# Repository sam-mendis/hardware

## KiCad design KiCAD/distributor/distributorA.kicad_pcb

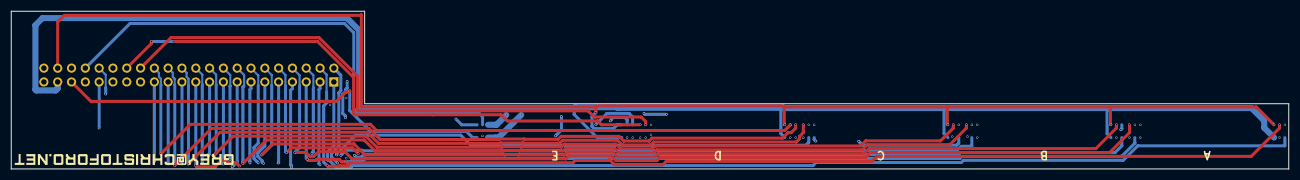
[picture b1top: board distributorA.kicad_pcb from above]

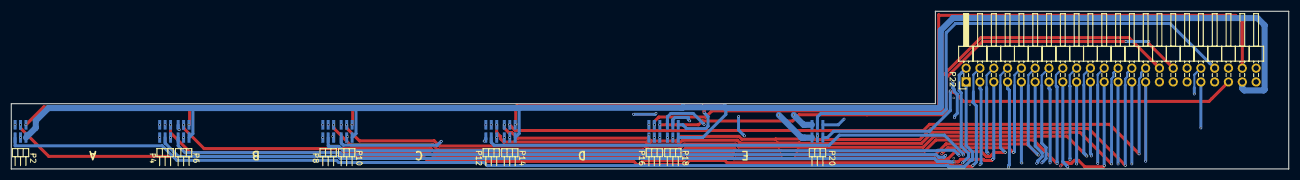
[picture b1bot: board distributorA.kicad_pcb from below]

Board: 4 copper layers, 235.0 x 29.0 mm, 11 parts (11 on the bottom side), 44 nets.

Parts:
P2, P4, P6, P8, P10, P12, P14, P16, P18, P20: CONN_02X03; FTMH-103-03-L-DH
P22: CONN_02X22; Pin_Header_Angled_2x22_Pitch2.54mm

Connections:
+3V3: P2.1, P6.1, P10.1, P14.1, P18.1, P22.41
+5V: P4.5, P8.5, P12.5, P16.5, P20.5, P22.43
A1_I: P2.3, P22.3
A1_V: P2.4, P22.4
A3_I: P4.3, P22.5
A3_V: P4.4, P22.6
A5_I: P4.1, P22.7
A5_V: P4.2, P22.8
AL_I: P2.5, P22.1
AL_V: P2.6, P22.2
B1_I: P6.3, P22.11
B1_V: P6.4, P22.12
B3_I: P8.3, P22.13
B3_V: P8.4, P22.14
B5_I: P8.1, P22.15
B5_V: P8.2, P22.16
BL_I: P6.5, P22.9
BL_V: P6.6, P22.10
C1_I: P10.3, P22.19
C1_V: P10.4, P22.20
C3_I: P12.3, P22.21
C3_V: P12.4, P22.22
C5_I: P12.1, P22.23
C5_V: P12.2, P22.24
CL_I: P10.5, P22.17
CL_V: P10.6, P22.18
D1_I: P14.3, P22.27
D1_V: P14.4, P22.28
D3_I: P16.3, P22.29
D3_V: P16.4, P22.30
D5_I: P16.1, P22.31
D5_V: P16.2, P22.32
DL_I: P14.5, P22.25
DL_V: P14.6, P22.26
E1_I: P18.3, P22.35
E1_V: P18.4, P22.36
E3_I: P20.3, P22.37
E3_V: P20.4, P22.38
E5_I: P20.1, P22.39
E5_V: P20.2, P22.40
EL_I: P18.5, P22.33
EL_V: P18.6, P22.34
GND: P4.6, P8.6, P12.6, P16.6, P20.6, P22.44
SCK: P2.2, P6.2, P10.2, P14.2, P18.2, P22.42

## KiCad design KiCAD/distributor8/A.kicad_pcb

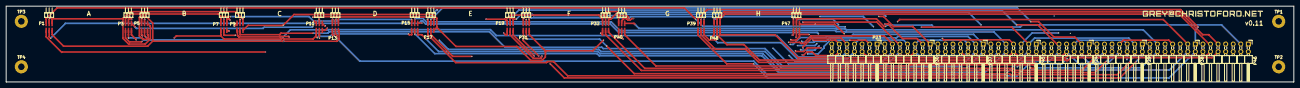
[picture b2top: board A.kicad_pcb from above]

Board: 4 copper layers, 431.8 x 25.4 mm, 28 parts (0 on the bottom side), 67 nets.

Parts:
P1, P3, P5, P7, P9, P11, P13, P15, P17, P19, P31, P32, P39, P40, P47, P48: CONN_02X03; FTMH-103-03-L-DH
P23, P24, P29, P30, P37, P38, P45, P46: CONN_02X07; Pin_Header_Angled_2x07_Pitch2.54mm
TP1, TP2, TP3, TP4: TEST; MountingHole_2.2mm_M2_Pad

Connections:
A0_I: P1.2, P23.2
A0_V: P1.1, P23.1
A2_I: P1.4, P23.4
A2_V: P1.3, P23.3
A4_I: P3.4, P23.10
A4_V: P3.3, P23.9
AR_I: P3.6, P23.12
AR_V: P3.5, P23.11
B0_I: P5.2, P30.2
B0_V: P5.1, P30.1
B2_I: P5.4, P30.4
B2_V: P5.3, P30.3
B4_I: P7.4, P30.10
B4_V: P7.3, P30.9
BR_I: P7.6, P30.12
BR_V: P7.5, P30.11
C0_I: P9.2, P37.2
C0_V: P9.1, P37.1
C2_I: P9.4, P37.4
C2_V: P9.3, P37.3
C4_I: P11.4, P37.10
C4_V: P11.3, P37.9
CR_I: P11.6, P37.12
CR_V: P11.5, P37.11
D0_I: P13.2, P45.2
D0_V: P13.1, P45.1
D2_I: P13.4, P45.4
D2_V: P13.3, P29.3, P31.3, P45.3
D4_I: P15.4, P45.10
D4_V: P15.3, P45.9
DR_I: P15.6, P45.12
DR_V: P15.5, P45.11
E0_I: P17.2, P24.2
E0_V: P17.1, P24.1
E2_I: P17.4, P24.4
E2_V: P17.3, P24.3
E4_I: P19.4, P24.10
E4_V: P19.3, P24.9
ER_I: P19.6, P24.12
ER_V: P19.5, P24.11
F0_I: P38.2, P39.2
F0_V: P38.1, P39.1
F2_I: P38.4, P39.4
F2_V: P38.3, P39.3
F4_I: P38.10, P40.4
F4_V: P38.9, P40.3
FR_I: P38.12, P40.6
FR_V: P38.11, P40.5
G0_I: P46.2, P47.2
G0_V: P46.1, P47.1
G2_I: P46.4, P47.4
G2_V: P46.3, P47.3
G4_I: P46.10, P48.4
G4_V: P46.9, P48.3
GR_I: P46.12, P48.6
GR_V: P46.11, P48.5
H0_I: P29.2, P31.2
H0_V: P29.1, P31.1
H2_I: P29.4, P31.4
H4_I: P29.10, P32.4
H4_V: P29.9, P32.3
HR_I: P29.12, P32.6
HR_V: P29.11, P32.5
MISO: P1.5, P5.5, P9.5, P13.5, P17.5, P23.5, P24.5, P29.5, P30.5, P31.5, P37.5, P38.5, P39.5, P45.5, P46.5, P47.5
MOSI: P1.6, P5.6, P9.6, P13.6, P17.6, P23.6, P24.6, P29.6, P30.6, P31.6, P37.6, P38.6, P39.6, P45.6, P46.6, P47.6
SCL: P3.1, P7.1, P11.1, P15.1, P19.1, P23.7, P24.7, P29.7, P30.7, P32.1, P37.7, P38.7, P40.1, P45.7, P46.7, P48.1
SDA: P3.2, P7.2, P11.2, P15.2, P19.2, P23.8, P24.8, P29.8, P30.8, P32.2, P37.8, P38.8, P40.2, P45.8, P46.8, P48.2

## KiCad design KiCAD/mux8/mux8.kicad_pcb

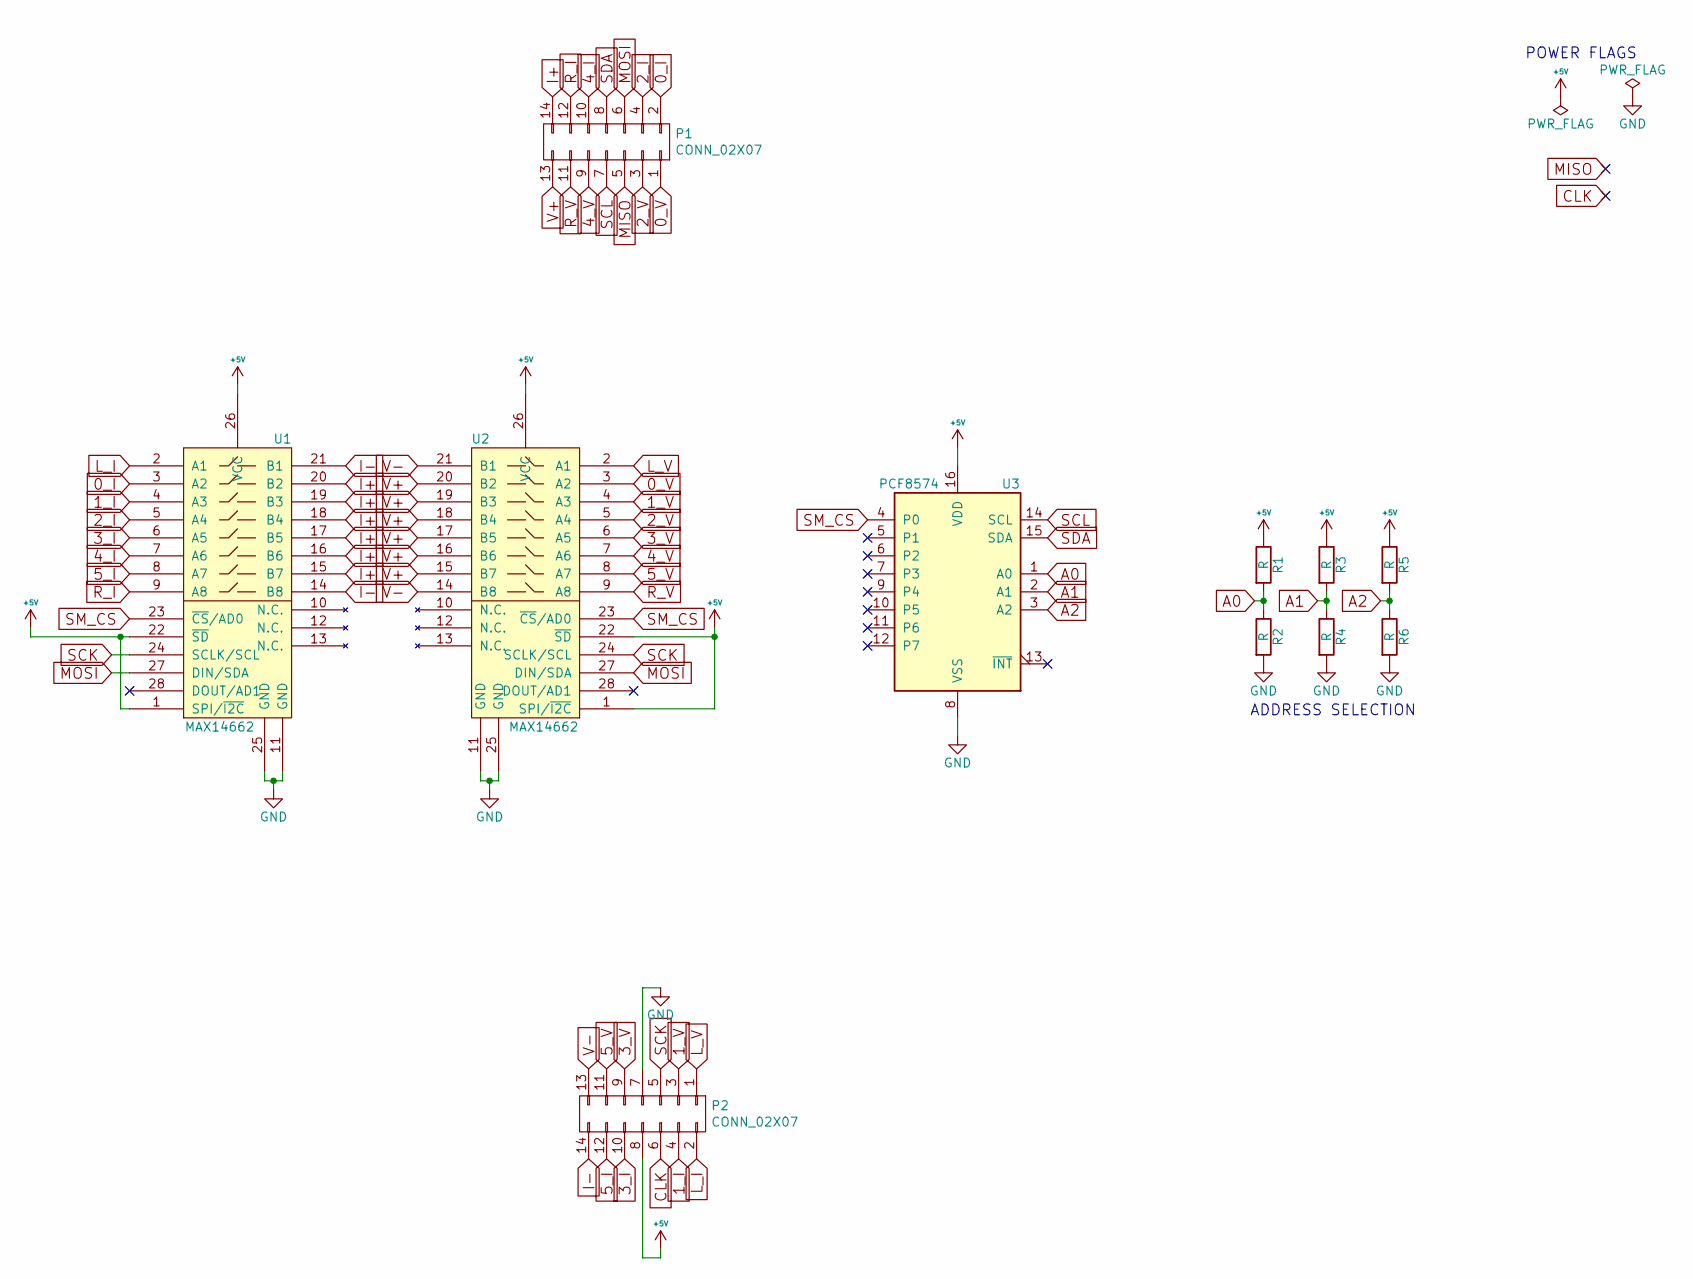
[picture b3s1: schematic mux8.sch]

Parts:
P1: CONN_02X07; SSM-107-L-DV
P2: CONN_02X07; SSM-107-L-DV-INV
R1, R2, R3, R4, R5, R6: R; R_0402
U1, U2: MAX14662; QFN-28-1EP_4x4mm_Pitch0.4mm
U3: PCF8574; SO-16-W

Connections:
0_I: P1.2, U1.3 (A2)
0_V: P1.1, U2.3 (A2)
1_I: P2.4, U1.4 (A3)
1_V: P2.3, U2.4 (A3)
2_I: P1.4, U1.5 (A4)
2_V: P1.3, U2.5 (A4)
3_I: P2.10, U1.6 (A5)
3_V: P2.9, U2.6 (A5)
4_I: P1.10, U1.7 (A6)
4_V: P1.9, U2.7 (A6)
5_I: P2.12, U1.8 (A7)
5_V: P2.11, U2.8 (A7)
+5V: P2.8, R1.1, R3.1, R5.1, U1.1 (SPI/~I2C), U1.22 (~SD), U1.26 (VCC), U2.1 (SPI/~I2C), U2.22 (~SD), U2.26 (VCC), U3.16 (VDD)
A0: R1.2, R2.1, U3.1 (A0)
A1: R3.2, R4.1, U3.2 (A1)
A2: R5.2, R6.1, U3.3 (A2)
CLK: P2.6
GND: P2.7, R2.2, R4.2, R6.2, U1.11 (GND), U1.25 (GND), U2.11 (GND), U2.25 (GND), U3.8 (VSS)
I+: P1.14, U1.15 (B7), U1.16 (B6), U1.17 (B5), U1.18 (B4), U1.19 (B3), U1.20 (B2)
I-: P2.14, U1.14 (B8), U1.21 (B1)
L_I: P2.2, U1.2 (A1)
L_V: P2.1, U2.2 (A1)
MISO: P1.5
MOSI: P1.6, U1.27 (DIN/SDA), U2.27 (DIN/SDA)
R_I: P1.12, U1.9 (A8)
R_V: P1.11, U2.9 (A8)
SCK: P2.5, U1.24 (SCLK/SCL), U2.24 (SCLK/SCL)
SCL: P1.7, U3.14 (SCL)
SDA: P1.8, U3.15 (SDA)
SM_CS: U1.23 (~CS~/AD0), U2.23 (~CS~/AD0), U3.4 (P0)
V+: P1.13, U2.15 (B7), U2.16 (B6), U2.17 (B5), U2.18 (B4), U2.19 (B3), U2.20 (B2)
V-: P2.13, U2.14 (B8), U2.21 (B1)

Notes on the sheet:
ADDRESS SELECTION
POWER FLAGS

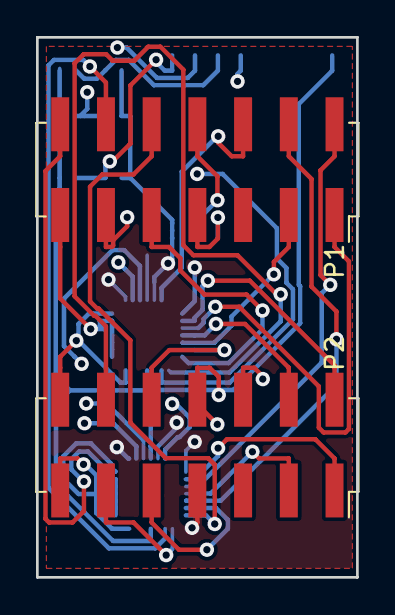
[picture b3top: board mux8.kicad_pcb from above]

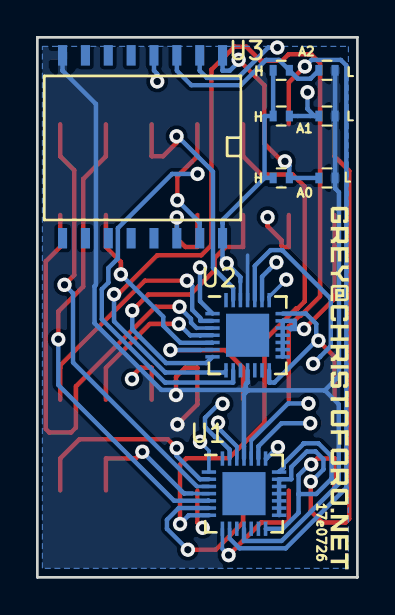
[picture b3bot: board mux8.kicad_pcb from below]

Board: 4 copper layers, 17.8 x 30.0 mm, 11 parts (9 on the bottom side), 30 nets.

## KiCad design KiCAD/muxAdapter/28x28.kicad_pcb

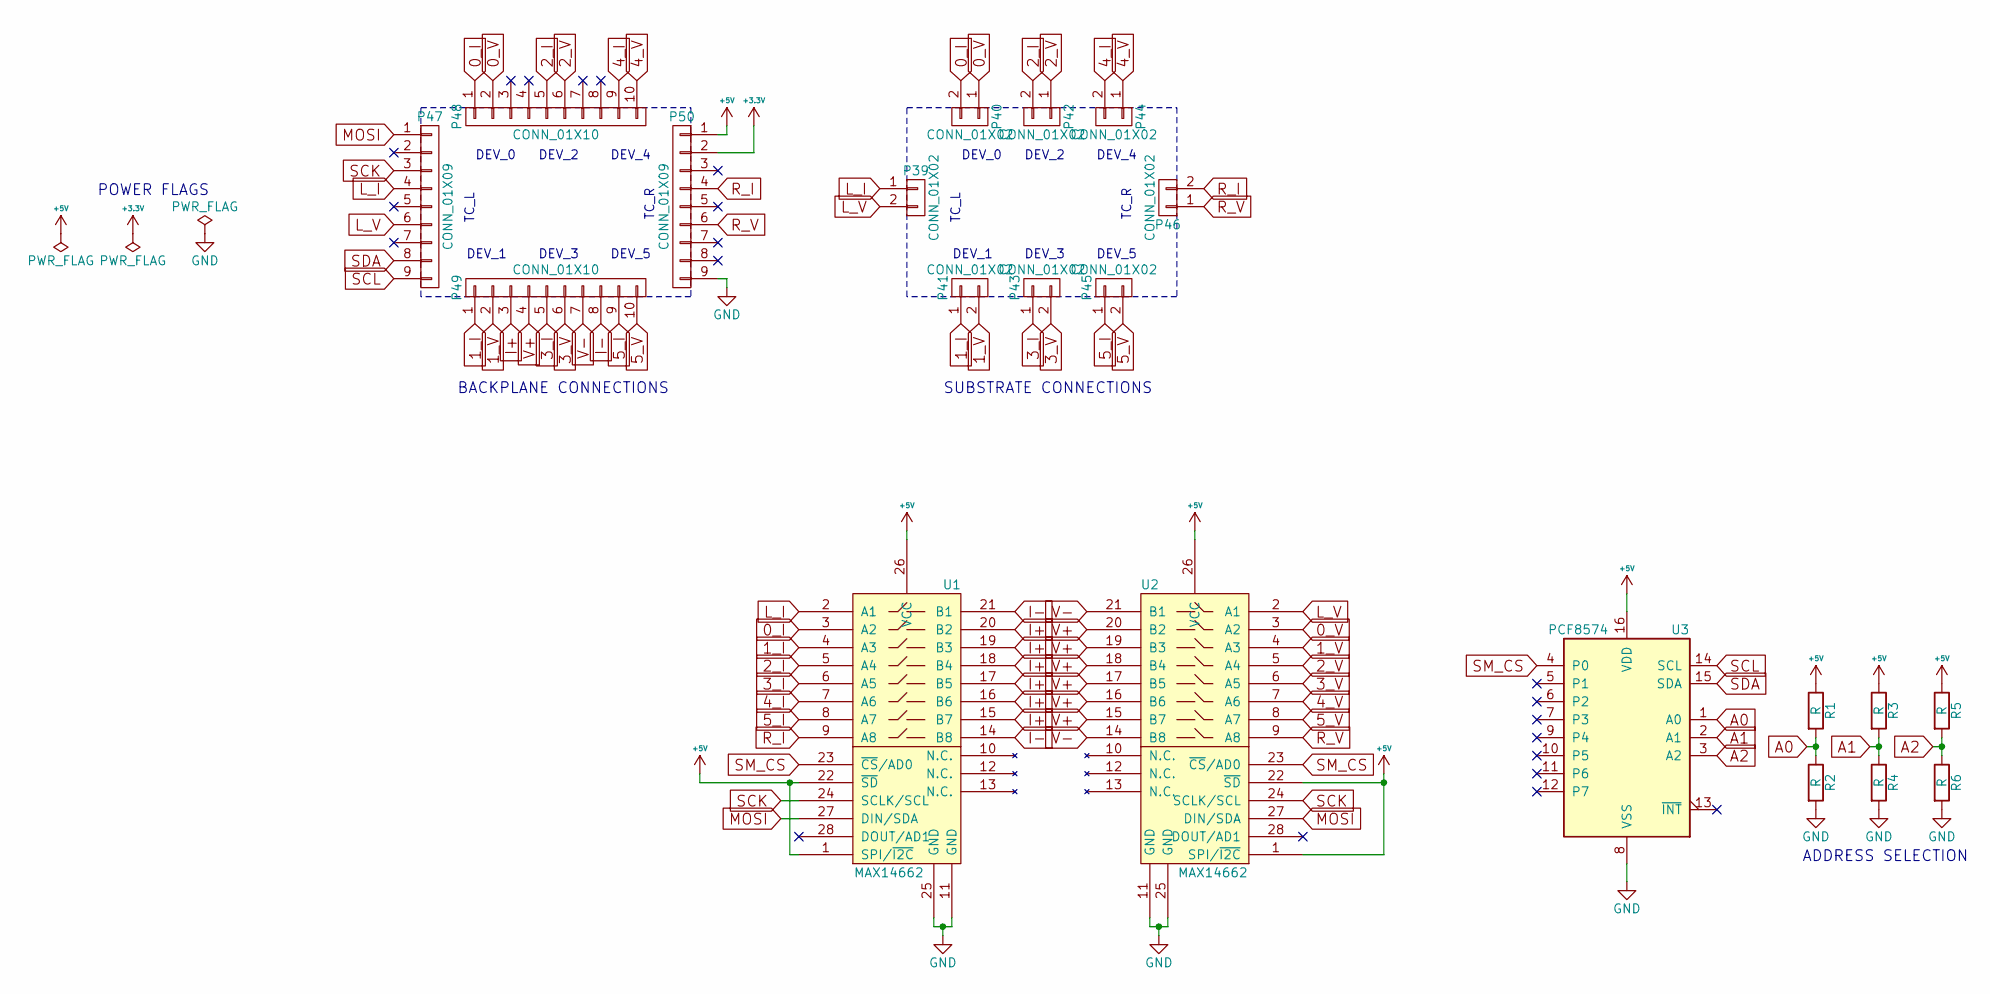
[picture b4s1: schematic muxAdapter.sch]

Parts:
P39, P40, P41, P42, P43, P44, P45, P46: CONN_01X02; 812-22-002-30-007101
P47, P50: CONN_01X09; TSM-109-01-T-SV
P48: CONN_01X10; TSM-110-01-T-SV
P49: CONN_01X10; TSM-110-01-T-SV-INV
R1, R2, R3, R4, R5, R6: R; R_0402
U1, U2: MAX14662; QFN-28-1EP_4x4mm_Pitch0.4mm
U3: PCF8574; SO-16-W

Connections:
0_I: P40.2, P48.1, U1.3 (A2)
0_V: P40.1, P48.2, U2.3 (A2)
1_I: P41.1, P49.1, U1.4 (A3)
1_V: P41.2, P49.2, U2.4 (A3)
2_I: P42.2, P48.5, U1.5 (A4)
2_V: P42.1, P48.6, U2.5 (A4)
3_I: P43.1, P49.5, U1.6 (A5)
3_V: P43.2, P49.6, U2.6 (A5)
4_I: P44.2, P48.9, U1.7 (A6)
4_V: P44.1, P48.10, U2.7 (A6)
5_I: P45.1, P49.9, U1.8 (A7)
5_V: P45.2, P49.10, U2.8 (A7)
+3V3: P50.2
+5V: P50.1, R1.1, R3.1, R5.1, U1.1 (SPI/~I2C), U1.22 (~SD), U1.26 (VCC), U2.1 (SPI/~I2C), U2.22 (~SD), U2.26 (VCC), U3.16 (VDD)
A0: R1.2, R2.1, U3.1 (A0)
A1: R3.2, R4.1, U3.2 (A1)
A2: R5.2, R6.1, U3.3 (A2)
GND: P50.9, R2.2, R4.2, R6.2, U1.11 (GND), U1.25 (GND), U2.11 (GND), U2.25 (GND), U3.8 (VSS)
I+: P49.3, U1.15 (B7), U1.16 (B6), U1.17 (B5), U1.18 (B4), U1.19 (B3), U1.20 (B2)
I-: P49.8, U1.14 (B8), U1.21 (B1)
L_I: P39.1, P47.4, U1.2 (A1)
L_V: P39.2, P47.6, U2.2 (A1)
MOSI: P47.1, U1.27 (DIN/SDA), U2.27 (DIN/SDA)
R_I: P46.2, P50.4, U1.9 (A8)
R_V: P46.1, P50.6, U2.9 (A8)
SCK: P47.3, U1.24 (SCLK/SCL), U2.24 (SCLK/SCL)
SCL: P47.9, U3.14 (SCL)
SDA: P47.8, U3.15 (SDA)
SM_CS: U1.23 (~CS~/AD0), U2.23 (~CS~/AD0), U3.4 (P0)
V+: P49.4, U2.15 (B7), U2.16 (B6), U2.17 (B5), U2.18 (B4), U2.19 (B3), U2.20 (B2)
V-: P49.7, U2.14 (B8), U2.21 (B1)

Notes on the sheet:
DEV_1
DEV_3
DEV_5
DEV_0
DEV_2
DEV_4
TC_L
TC_R
BACKPLANE CONNECTIONS
SUBSTRATE CONNECTIONS
ADDRESS SELECTION
POWER FLAGS

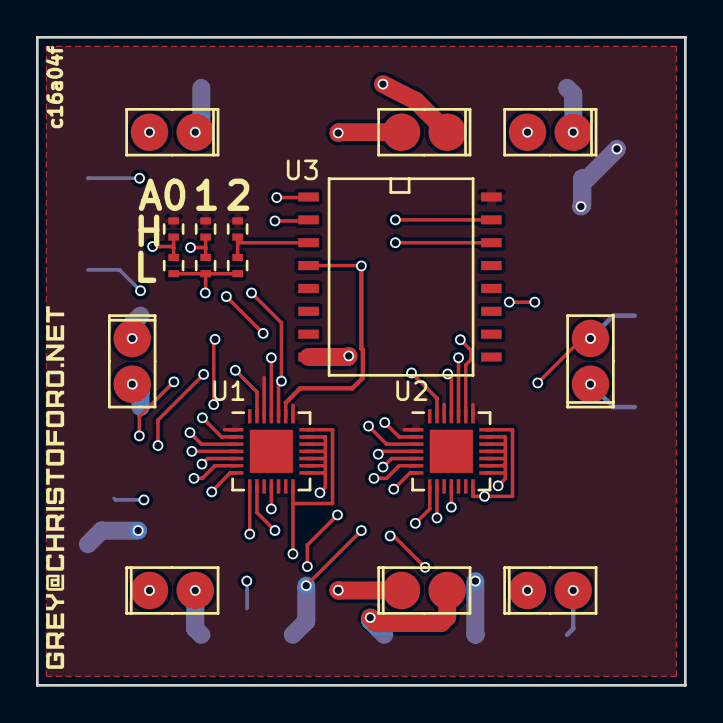
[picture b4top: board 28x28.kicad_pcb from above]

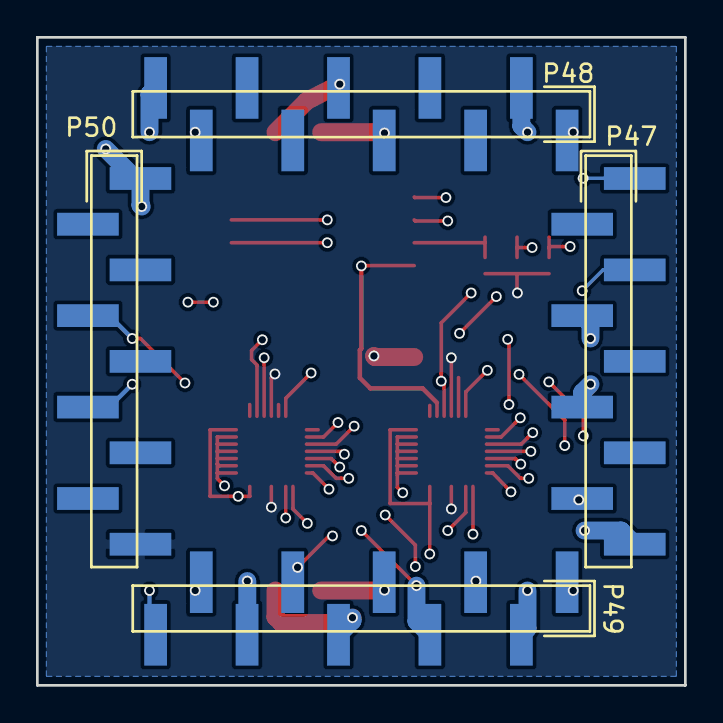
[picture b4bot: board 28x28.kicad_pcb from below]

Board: 4 copper layers, 36.0 x 36.0 mm, 21 parts (4 on the bottom side), 30 nets.

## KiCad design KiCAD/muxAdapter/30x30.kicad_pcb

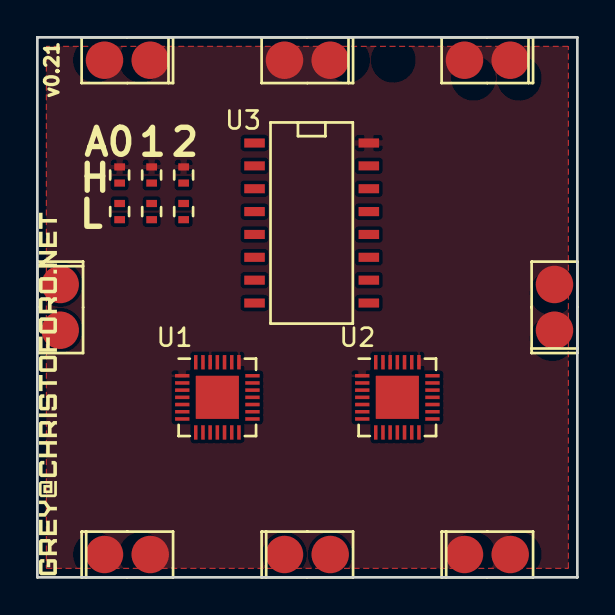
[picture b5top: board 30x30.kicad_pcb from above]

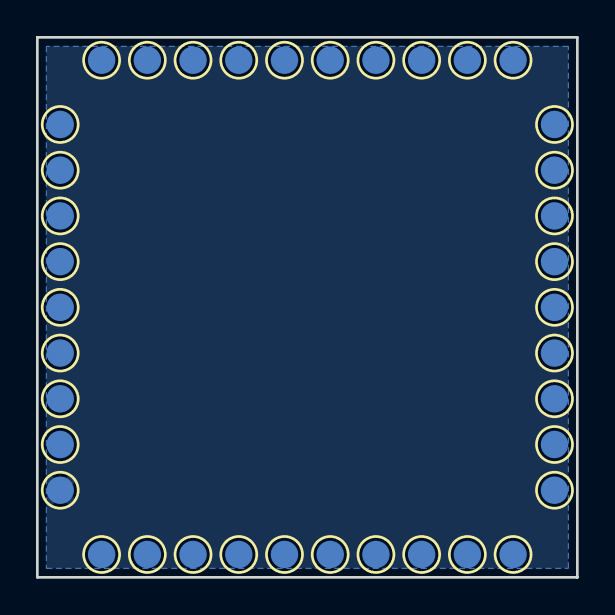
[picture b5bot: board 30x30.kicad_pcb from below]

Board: 4 copper layers, 30.0 x 30.0 mm, 55 parts (38 on the bottom side), 31 nets, no tracks yet.

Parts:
P1, P2, P3, P4, P5, P6, P7, P8, P9, P10, P11, P12, P13, P14, P15, P16, P17, P18, P19, P20, P21, P22, P23, P24, P25, P26, P27, P28, P29, P30, P31, P32, P33, P34, P35, P36, P37, P38: CONN_01X01; 0508-0-00-15-00-00-03-0
P39, P40, P41, P42, P43, P44, P45, P46: CONN_01X02; 812-22-002-30-007101
R1, R2, R3, R4, R5, R6: R; R_0402
U1, U2: MAX14662; QFN-28-1EP_4x4mm_Pitch0.4mm
U3: PCF8574; SO-16-N

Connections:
0_I: P10.1, P40.2, U1.3
0_V: P12.1, P40.1, U2.3
1_I: P11.1, P41.1, U1.4
1_V: P13.1, P41.2, U2.4
2_I: P18.1, P42.2, U1.5
2_V: P20.1, P42.1, U2.5
3_I: P19.1, P43.1, U1.6
3_V: P21.1, P43.2, U2.6
4_I: P26.1, P44.2, U1.7
4_V: P28.1, P44.1, U2.7
5_I: P27.1, P45.1, U1.8
5_V: P29.1, P45.2, U2.8
+5V: P30.1, R1.1, R3.1, R5.1, U1.1, U1.22, U1.26, U2.1, U2.22, U2.26, U3.16
A0: R1.2, R2.1, U3.1
A1: R3.2, R4.1, U3.2
A2: R5.2, R6.1, U3.3
GND: P38.1, R2.2, R4.2, R6.2, U1.11, U1.25, U2.11, U2.25, U3.8
I+: P15.1, U1.15, U1.16, U1.17, U1.18, U1.19, U1.20
I-: P25.1, U1.14, U1.21
L_I: P4.1, P39.1, U1.2
L_V: P6.1, P39.2, U2.2
MOSI: P1.1, U1.27, U2.27
unnamed: U1.23, U2.28
R_I: P33.1, P46.2, U1.9
R_V: P35.1, P46.1, U2.9
SCK: P3.1, U1.24, U2.24
SCL: P9.1, U3.14
SDA: P8.1, U3.15
SM_CS: U2.23, U3.4
V+: P17.1, U2.15, U2.16, U2.17, U2.18, U2.19, U2.20
V-: P23.1, U2.14, U2.21
